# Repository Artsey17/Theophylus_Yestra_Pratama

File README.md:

# Theophylus_Yestra_Pratama
Task kandidat MSIB Electronics Engineer PT. Widya Inovasi Indonesia
Berikut Hasil Jawaban dari Soal Hardware Engineer 

Yth. Bapak/Ibu HRD Widya Robotics,

Perkenalkan, saya Theophylus Yestra Pratama. Dengan penuh hormat, saya bermaksud untuk mengumpulkan hasil jawaban yang telah saya kerjakan sebagai bagian dari Task dalam proses Internship untuk posisi Hardware Engineer.

Saya telah berusaha semaksimal mungkin dalam menyelesaikan semua tugas yang diberikan, dengan harapan hasil yang saya kumpulkan dapat memenuhi harapan Bapak/Ibu.

Saya sangat menghargai kesempatan ini dan berterima kasih atas perhatian serta waktu yang Bapak/Ibu berikan, Terima kasih.

Hormat saya,
Theophylus Yestra Pratama

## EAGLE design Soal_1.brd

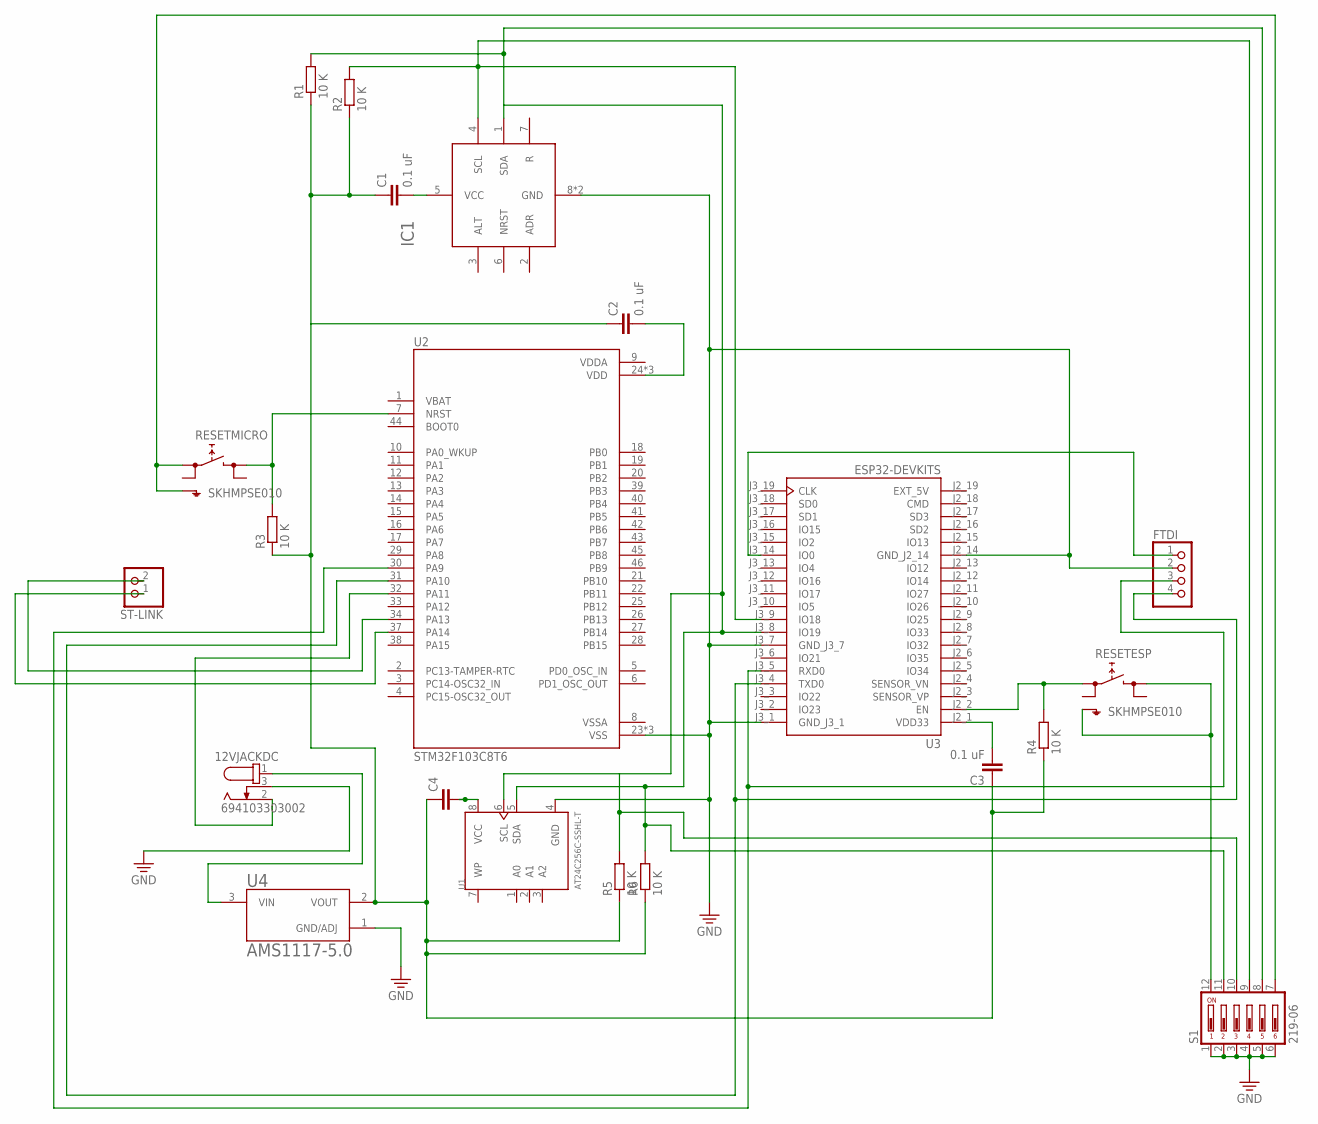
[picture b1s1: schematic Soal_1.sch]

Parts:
12VJACKDC: 694103303002
C1, C2, C3: 0.1 uF; C5B3.5
C4: C5/3.5; C5B3.5
FTDI: PINHD-1X4; 1X04
IC1: SHT31; SON50P250X250X90-9T110X180N
R1, R2, R3, R4, R5, R6: 10 K; 0207/10
RESETESP: SKHMPSE010; SKHMPXE010
RESETMICRO: SKHMPSE010; SKHMPXE010
S1: 219-06; CTS-219-06
ST-LINK: PINHD-1X2; 1X02
U1: AT24C256C-SSHL-T; SOIC127P600X175-8N
U2: STM32F103C8T6; QFP50P900X900X160-48N
U3: ESP32-DEVKITS; MODULE_ESP32-DEVKITS
U4: AMS1117-5.0; SOT229P700X180-4N

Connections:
EXT_5V: U3.J2_19 (EXT_5V)
GND: 12VJACKDC.3, FTDI.2, IC1.8 (GND), IC1.9 (GND), S1.1, S1.2, S1.3, S1.4, S1.5, S1.6, U1.4 (GND), U2.23 (VSS), U2.35 (VSS), U2.47 (VSS), U3.J2_14 (GND_J2_14), U3.J3_1 (GND_J3_1), U3.J3_7 (GND_J3_7), U4.1 (GND/ADJ)
unnamed: 12VJACKDC.1, U4.3 (VIN)
unnamed: C4.2, U1.8 (VCC)
unnamed: C1.1, C2.1, C3.1, C4.1, R1.1, R2.1, R3.1, R4.1, R5.1, R6.1, U4.2 (VOUT)
unnamed: C1.2, IC1.5 (VCC)
unnamed: C2.2, U2.24 (VDD), U2.36 (VDD), U2.48 (VDD)
unnamed: C3.2, U3.J2_1 (VDD33)
unnamed: R4.2, RESETESP.1 (1.1), U3.J2_2 (EN)
unnamed: RESETESP.3 (2.1), RESETESP.5 (SH), S1.12
unnamed: FTDI.4, U2.31 (PA10), U3.J3_4 (TXD0)
unnamed: FTDI.3, U2.30 (PA9), U3.J3_5 (RXD0)
unnamed: RESETMICRO.1 (1.1), RESETMICRO.5 (SH), S1.7
unnamed: R3.2, RESETMICRO.3 (2.1), U2.7 (NRST)
unnamed: IC1.4 (SCL), R2.2, S1.9, U3.J3_9 (IO18)
unnamed: IC1.1 (SDA), R1.2, R5.2, R6.2, S1.8, S1.10, S1.11, U1.5 (SDA), U1.6 (SCL), U3.J3_8 (IO19)
unnamed: 12VJACKDC.2, U2.32 (PA11)
unnamed: ST-LINK.2, U2.34 (PA13)
unnamed: ST-LINK.1, U2.37 (PA14)
unnamed: FTDI.1, U3.J3_14 (IO0)
VDDA: U2.9 (VDDA)
VSSA: U2.8 (VSSA)

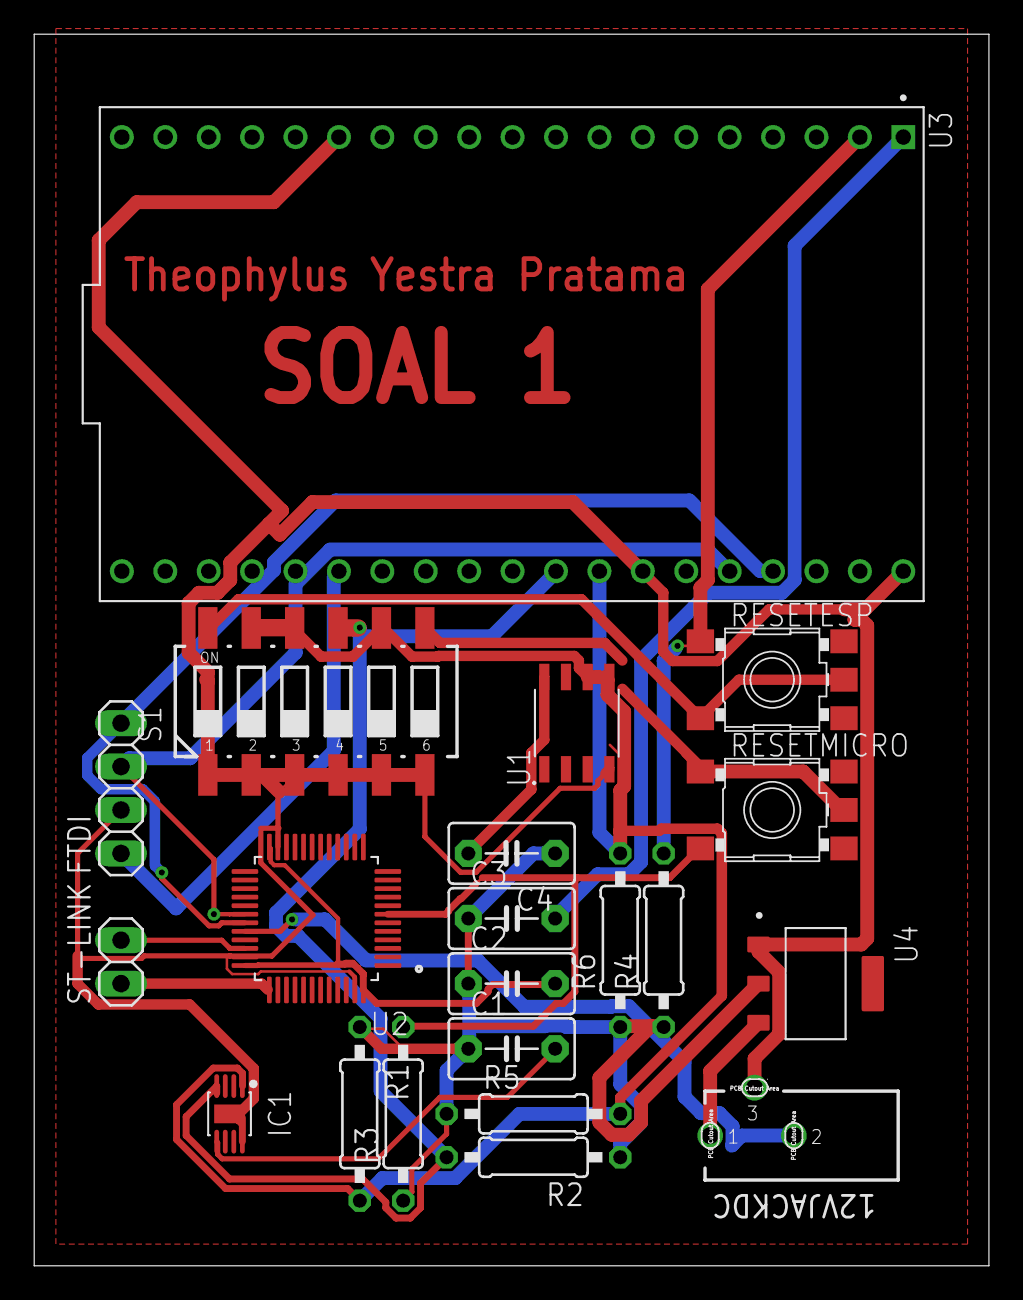
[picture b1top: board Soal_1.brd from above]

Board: 2 copper layers, 55.8 x 72.0 mm, 21 parts (0 on the bottom side), 19 nets.

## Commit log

2024-08-29 Soal_1
2024-08-29 Soal hardware Engineer
2024-08-29 README.md
